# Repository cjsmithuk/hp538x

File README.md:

# HP 538xA frequency counter OCXO adapter board

This project allows a cheap CTI OSC5A2B02 to be installed in an HP 5384A, 
5385A or 5386A frequency counter instead of the original crystal or TCXO 
reference.

## Notes

Status: **PRODUCTION**

* Gerbers are available in [gerbers/](gerbers/)
* KiCad project avalable in [kicad/](kicad/)
* JLCPCB can provide boards.
* Please don't ask me for any boards or parts!

## BOM

| Reference | Part |
| -- | -- |
| C1-6 | 0805 100nF 50V X7R MLCC |
| L1 | 1812 1.2uH >800mA i.e. Murata LQH43NH1R2K03L |
| O1 | CTI OSC5A2B02 (available cheaply from eBay and AliExpress sellers) |
| U1 | MAX6064BEUR+T |
| RV1 | 5K Bourns 3296Y vertical |
| J1-4 | standard 2.54mm header pins (8 needed in total) |
| R95 | 100R 0.25W metal film TH resistor |

## Equipment

* Soldering iron
* 50MHz+ oscilloscope
* DMM
* 10MHz reference for calibration (Leo Bodnar GPSDO)
* Usual hand tools

## OCXO check out

Before performing this procedure it is advisable to check the OCXO function. If it arrives still soldered to a cut board (mine did), desolder it carefully.

1. Refer to the datasheet in the reference documentation section.
2. Attach 5v power supply to the OCXO
3. Attach oscilloscope 10x probe to the output/ground.
4. Check OCXO heats
5. Check OCXO output at 10MHz.

## Construction

1. Obtain the parts.
2. Install C1-6
3. Install L1
4. Install U1
5. Install J1-4 so they stick out from the bottom.
6. Remove the plastic spacers off 4 more pins and push onto the protruding pins to raise the height of the board from the host counter.
7. Install RV1
8. Orient the board SMD parts facing you, text upright and apply 5v to the top right (+) and middle right pins (-)
9. Measure voltage at U1/C6 junction. Should be approx 4V
10. Install O1.
11. Reconnect 5v supply and validate current < 600mA and > 300mA.
12. Wait for current to reduce to < 300mA. OCXO should be warm.
13. Orient the board SMD parts facing you, text upright and connect scope to bottom right pin and ground. Validate 10MHz square wave. Approx 5v p-p.

## Installation

1. Remove vinyl strips from side of counter
2. Remove feet
3. Remove 4 fixing screws in base
4. Release top of unit and slide off vertically
5. Remove 4 black mounting posts and two spring clips from side of unit
6. Remove two fixing screws holding base of case onto PCB
7. Remove base of case from PCB
8. As per service manual 2-52, remove C61-66, R96-99, R110, Q13, Q14, Y1C, W2. This is easier done if the GPIB interface card is removed first. If your counter has the TCXO, you only need to remove Y1B, R95 and W2.
9. Jumper L5 (short)
10. Replace R95 with 100R 0.25W.
11. Install the PCB in the position marked OVEN OSCILLATOR.
12. Place in bottom of case and reinstall the two fixing screws.

## Test procedure

1. Make sure reference switch on rear is set to internal.
2. Connect the mains but do not power the unit up.
3. Check that the OCXO module is warming up (finger is fine) in standby mode. 
4. Power up the unit.
5. Press CHECK on the front panel and make sure it reads 10.00000MHz
6. Reinstall GPIB board and proceed to adjustment section.

## Adjustment

1. Connect the counter reference output to your oscilloscope X channel
2. Connect your frequency standard output to your oscilloscope Y channel
3. Leave both units to warm for 2-4 hours.
4. Put the oscilloscope into X-Y mode and adjust gain until a loop is displayed.
5. Adjust the trimpot on the counter until the lissajous pattern is stable. This means both signals are at the same frequency.

## Reference documentation

* [CTI OSC5A2B02 datasheet](data/cti-osc5a2b02-datasheet.pdf)
* [CTI OSC5A2B02 drawings](data/cti-osc5a2b02-drawing.jpg)
* [MAX6064 datasheet](data/max606x-datasheet.pdf)

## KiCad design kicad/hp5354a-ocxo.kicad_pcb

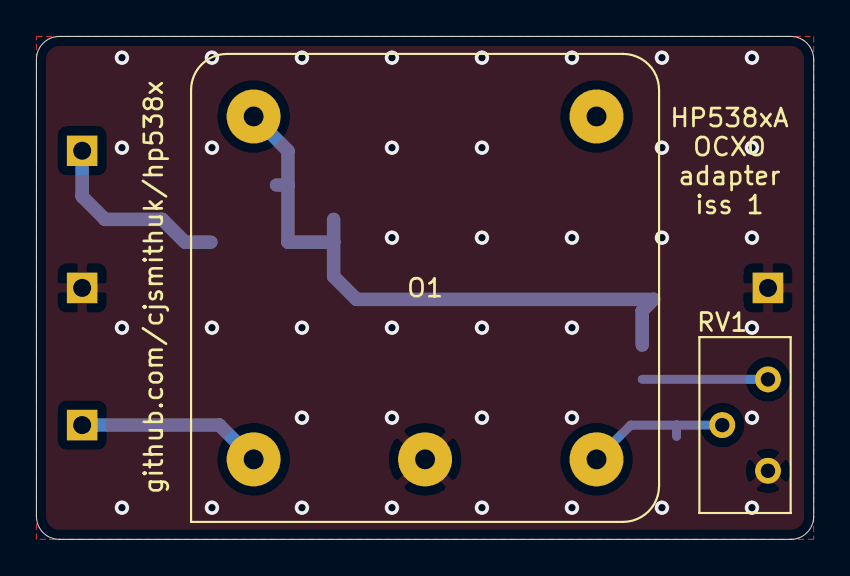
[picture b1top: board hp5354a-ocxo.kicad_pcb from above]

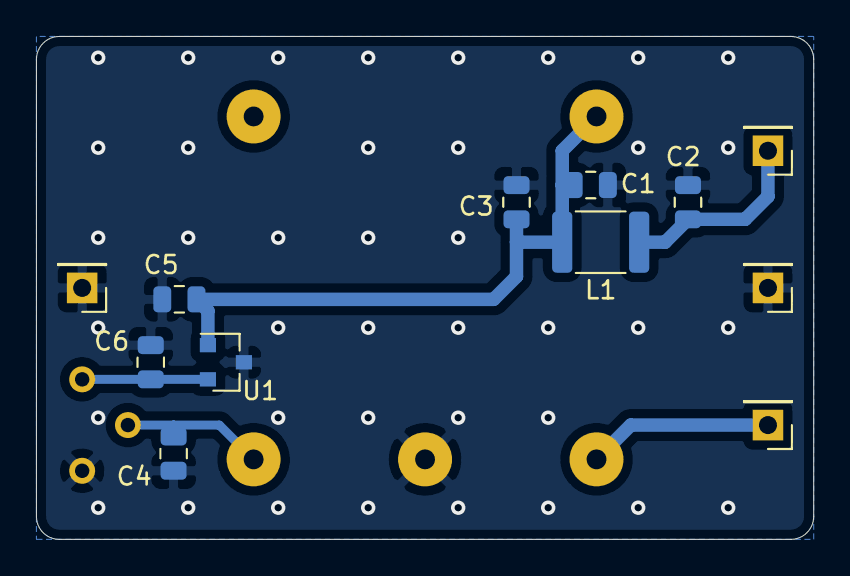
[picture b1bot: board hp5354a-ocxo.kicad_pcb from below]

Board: 2 copper layers, 43.2 x 27.9 mm, 14 parts (12 on the bottom side), 6 nets.

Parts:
C1, C2, C3, C4, C5, C6: 100n; C_0805_2012Metric
J1: 5V; PinHeader_1x01_P2.54mm_Vertical
J2: GND1; PinHeader_1x01_P2.54mm_Vertical
J3: GND2; PinHeader_1x01_P2.54mm_Vertical
J4: OUT; PinHeader_1x01_P2.54mm_Vertical
L1: 1.2u; L_1812_4532Metric
O1: osc5a2b02
RV1: 5k; Potentiometer_Bourns_3296Y_Vertical
U1: max6064; SOT-23

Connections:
+5V: C1.1, C3.1, C5.1, L1.2, O1.5, U1.1
/Vcont: C4.1, O1.3, RV1.2
GND: C1.2, C2.2, C3.2, C4.2, C5.2, C6.2, J2.1, J3.1, O1.2, RV1.1, U1.3
unnamed: C2.1, J1.1, L1.1
unnamed: C6.1, RV1.3, U1.2
unnamed: J4.1, O1.1

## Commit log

2021-03-21 Update README with project overview
2021-03-21 Upload issue 1 + docs
2021-03-27 Add reference documentation
2021-04-08 Update documentation
2021-04-08 finish docs, update images, move to prod status
2021-04-09 minor instructions fix
2021-04-23 move gerbers to their own dir
2021-04-23 Update gerbers link and text
2021-04-23 Add kicad project
2021-04-23 Add kicad link to README
